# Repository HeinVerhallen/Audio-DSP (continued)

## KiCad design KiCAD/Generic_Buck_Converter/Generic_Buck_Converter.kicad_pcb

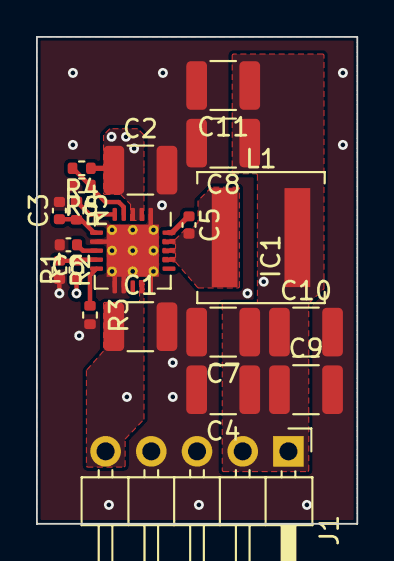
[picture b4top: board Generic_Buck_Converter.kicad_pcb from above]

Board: 4 copper layers, 17.8 x 27.0 mm, 20 parts (0 on the bottom side), 11 nets.

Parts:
C1, C2, C4, C7, C8, C9, C10, C11: C; C_1210_3225Metric
C3, C5, C6: C; C_0402_1005Metric
IC1: MAX17634C; TQFN-20-1EP_4x4mm_P0.5mm_EP2.9x2.9mm_ThermalVias_(JLCPCB_Co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
J1: Conn_01x05; PinHeader_1x05_P2.54mm_Horizontal
L1: L; L_Coilcraft_XAL6060-XXX
R1, R2, R3, R4, R5, R6: R; R_0402_1005Metric

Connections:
/Vin: C1.1, C2.1, IC1.2 (IN), IC1.3 (IN), IC1.14 (IN), J1.5, R4.1
/Vout: C4.1, C7.1, C8.1, C9.1, C10.1, C11.1, J1.1, J1.2, L1.2, R1.1
GND: C1.2, C2.2, C3.2, C4.2, C6.2, C7.2, C8.2, C9.2, C10.2, C11.2, IC1.1 (PGND), IC1.7 (SGND), IC1.11 (MODE/SYNC), IC1.12 (EXTVCC), IC1.15 (PGND), IC1.21 (EP), J1.3, J1.4, R2.2, R3.2, R6.2
unnamed: C5.2, IC1.17 (LX), IC1.18 (LX), IC1.19 (LX), L1.1
unnamed: C5.1, IC1.20 (BST)
unnamed: IC1.4 (EN/UVLO), R4.2, R6.1
unnamed: IC1.9 (FB), R1.2, R2.1
unnamed: C3.1, IC1.6 (INTVCC), R5.2
unnamed: IC1.5 (RESET), R5.1
unnamed: IC1.10 (RT), R3.1
unnamed: C6.1, IC1.8 (SS)

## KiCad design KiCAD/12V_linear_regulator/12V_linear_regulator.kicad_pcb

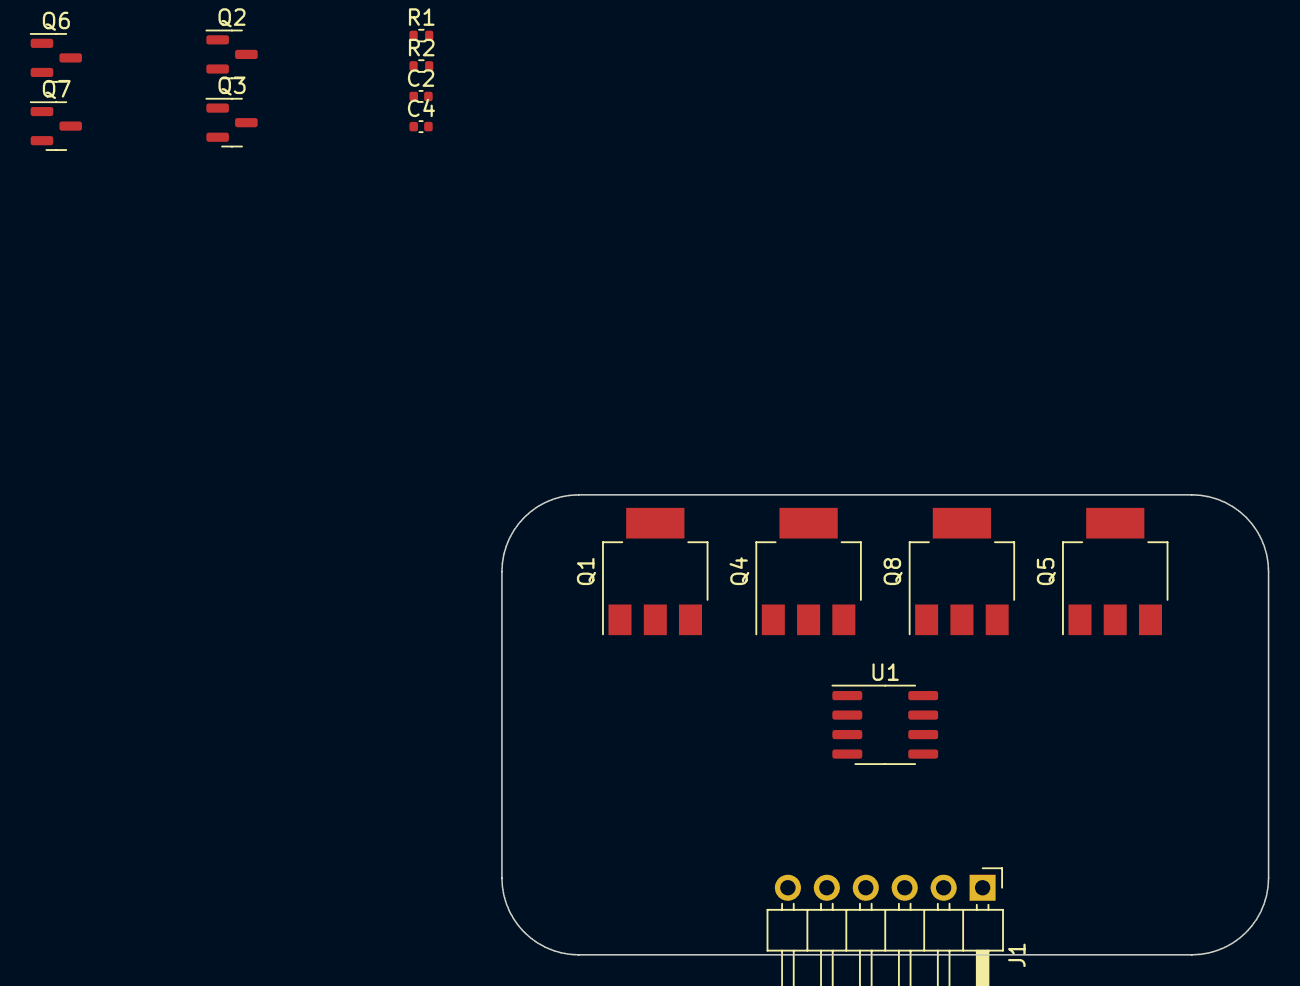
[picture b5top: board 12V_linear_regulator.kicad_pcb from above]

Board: 2 copper layers, 50.0 x 30.0 mm, 14 parts (0 on the bottom side), 8 nets, no tracks yet.

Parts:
C2, C4: 100p; C_0402_1005Metric
J1: Conn_01x06; PinHeader_1x06_P2.54mm_Horizontal
Q1, Q4: PZT2222AT3G; SOT-223
Q2, Q3: BC857; SOT-23
Q5, Q8: PZT2907AT3G; SOT-223
Q6, Q7: BC847; SOT-23
R1: 780R; R_0402_1005Metric
R2: 10k; R_0402_1005Metric
U1: LM4562; SOIC-8_3.9x4.9mm_P1.27mm

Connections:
+12V: J1.3, Q4.3
+15V: J1.1, Q1.2, Q1.4
GND: C4.2, J1.2, J1.5, R2.1
unnamed: C4.1, Q3.3 (C), U1.3 (+)
unnamed: Q2.1 (B), Q3.2 (E), R1.2
unnamed: Q2.3 (C), Q3.1 (B), R2.2
unnamed: Q1.3, Q2.2 (E), Q4.2, Q4.4, R1.1
unnamed: Q4.1, U1.1

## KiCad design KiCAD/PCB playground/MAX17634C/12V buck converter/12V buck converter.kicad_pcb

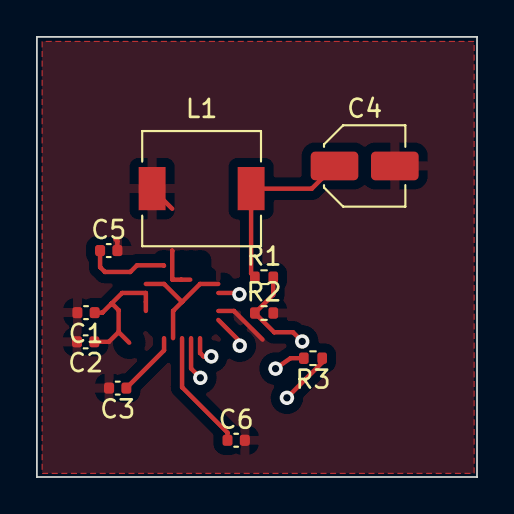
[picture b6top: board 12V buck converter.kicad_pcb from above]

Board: 4 copper layers, 24.5 x 24.5 mm, 10 parts (0 on the bottom side), 4 nets.

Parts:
C1, C2, C3, C5, C6: C; C_0402_1005Metric
C4: C; C_Elec_4x5.8
L1: L; L_6.3x6.3_H3
R1, R2, R3: R; R_0402_1005Metric

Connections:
/FB: R1.2, R2.1
/Vout: C4.1, L1.2, R1.1
Earth: C1.2, C2.2, C3.2, C4.2, C5.2, C6.2, L1.1, R2.2
unnamed: C1.1, C2.1

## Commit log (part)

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2023-04-13 Created audio sampler project
    Started with I2C protocol. Used I2C master from open-source file. Made initializer block which programs the WM8731 in the FPGA board using the I2C master block.
2023-04-13 Cleaned up
2023-04-15 Updated file structure to make it more clear
2023-04-17 Made the pdf of the SRD
2023-04-17 Updated SEPIC
2023-04-17 Added PCM1804
2023-04-18 Added symbol and footprint for general buck converter
2023-04-18 Worked on main board
2023-04-18 Add Generic PCB to Git
2023-04-18 Worked on KiCAD
2023-04-18 Worked a bit on the main board
2023-04-19 Update library, updated 3D model path
2023-04-19 fixed 3D viewer
2023-04-19 Push so we all have the same
2023-04-19 Updated main step
2023-04-19 2 codes for the i2s encoder
2023-04-19 Deleted the playground test
2023-04-20 fixed symbols excluding from board
2023-04-20 update kicad
2023-04-20 Buck PCB
2023-04-24 Update Audio sampler VHDL
    Created I2S encoder and decoder. Tested the code but the audio has a lot of noise.
2023-04-24 Updated Audio sampler VHDL
    Imported I2S_transceiver VHDL block from internet. This block uses the audio-codec inside the FPGA board as a slave. This has been tested and the audio is sampled correctly without any noise.
2023-04-24 Update Audio sampler
    Improved I2S encoder and decoder such that it now works. Tested with FPGA board and Audio came out correctly.
2023-04-25 Added 3D model 744871004
2023-04-25 Update Audio sampler
    Fixed bug where sampler worked at 32 bit but not at 24 bit. Now its able to sample at all bit resolutions. Saved .sof files for different scenarios.
2023-04-25 Made symbol and footprint for the FPGA board
2023-04-25 Update Audio sampler
    Created signal processor manager block.
    Created signal processor VHDL.
    Created shift register VHDL block.
    Implemented signal processor block with shift registers in signal processor manager.
2023-04-26 Worked on the linear voltage regulators
2023-04-28 Update SDD
    Wrote paragraph in architecture design chapter.
    Improved some text in system context design chapter.
2023-05-05 changes and additions to the sdd
    fixed a faulty piece of code in architecture and added stuff to UI
2023-05-08 kicad sepic update
2023-05-09 removed float specifier warning
2023-05-09 added parskip package
2023-05-09 Update SDD
    Update System architecture chapter
2023-05-09 Schematic orderlist update
2023-05-09 Updated background
2023-05-09 Worked on main board SCH
2023-05-10 Update SDD
    Updated architecture chapter
2023-05-10 Created Signal processor framework with FFT
2023-05-10 Created Matlab files for understanding FFT
2023-05-10 Worked on main board schematic
2023-05-10 Removed PDF files in Documentation folder
    Added pdf ignore in Documentation folder in Gitignore.
    Removed all PDF files in Documentation folder.
2023-05-10 Added black box representation
2023-05-11 Added Gerber + Excel-sheet
2023-05-16 Gerber_update
2023-05-16 Worked on SDD
2023-05-17 bestandsnaam wijziginen
2023-05-17 more pictuuuuures
2023-05-17 linear regulators changes
2023-05-22 update linear regulator pcb
2023-05-23 Matlab DFT with cosine and sine
    Created matlab script and simulink model to compute real and imaginary values of certain coefficients in input signal by multiplying input samples with sine and cosine for one period.
2023-05-23 Worked on main board schematic and PCB, added symbols to symbol library
2023-05-23 Worked on main board design
2023-05-24 linear
2023-05-24 Linear regulator schematic update
2023-05-24 update linear pcb
2023-05-24 Update fp-info-cache
2023-05-25 Matlab FFT + taylor series
    FFT_Radix2_DecimationInTime - Created first matlab tests where I implemented the FFT mathematics manually.
    TaylorSeries_sin_cos_generation - Updated the sinewave generation equation so it now works according to the horner mathematics.
2023-05-26 Test FPGA overclocking
    created new Quartus project to test PLL block capabilities to overclock the FPGA. This is possible up to a certain frequency. Highest frequency so far was 670MHz. See .sof files.
2023-05-30 Main board
2023-05-30 update linear and gerbers
2023-05-30 Mainboard buck_converter symbol update
2023-05-30 VU-meter design LTspice
2023-05-30 main PCB update DAC CH_1_2
2023-05-31 new gerbers
2023-05-31 added drill map files :)
2023-05-31 Completed ordering folder JLCPCB
2023-06-01 Test FPGA memory allocation VHDL
    Made a test program in VHDL to check how much memory is used by the FPGA for certain data arrays.
2023-06-05 Main board, ordering of PCBs and LTspice simulations
2023-06-05 Main PCB update
2023-06-05 Started UART protocol in VHDL
    Created a new quartus project for the UART protocol with the schematic of the basic blocks.
2023-06-05 created and tested uart parts
    the receiving and transmitting block have been coded and tested
    The TX buffer is no finished
    The RX buffer is not started
    the clock divider is not started
2023-06-06 Ad good as finilized the main board schematic
2023-06-06 Finalizer main board schematic exept passive order links. Schematic ready for review
2023-06-07 Updated UART protocol
    finished simulating the system
    the hardware test is yet to be performed
2023-06-07 Creation of final report (MDD)
    Created the Module Design Document
2023-06-08 Main brd
2023-06-08 Added STEP file
2023-06-08 main pcb
2023-06-08 Schematic send to Ralph for review
2023-06-12 Main board update
2023-06-13 PCB Main update
2023-06-13 Matlab Effects
    added the matlab effects me and youri made
2023-06-13 Created multiplication VHDL code
    Multiplication VHDL code is capable of doing unsigned multiplication and std_logic_vector multiplication.
2023-06-14 updated and simulink
2023-06-14 Updated order forms and ordered components 14-06-2023
2023-06-15 added stuff to the latex file
2023-06-16 Update multiplier_rounder.vhd
    Implemented unsigned, signed and STD_LOGIC_VECTOR multiplication functions. The unsigned and STD_LOGIC_VECTOR got to work in a very small time. But the signed one was very tricky. But in this version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
2023-06-16 Main board update ADC and DAC
2023-06-19 Worked on MDD
2023-06-19 Create BPF_filter.vhd
    Made BPF filter with state space.
    So far the computation of the discrete state space coefficients work.
    The compression of the larger binary value to a smaller one works now for unsigned values
2023-06-19 Update VHDL value compressor
    Finished the unsigned and signed value compress functions. They have been tested thoroughly with the according .do file.
    The functions are cleaned up and comments are added.
2023-06-20 a lot
2023-06-20 updated UIController
    added page navigation through buttons
2023-06-20 updated UI design
    added the new designs for the signal routing and presets
2023-06-21 added debounce resistor
2023-06-22 Divided Realization chapter into seperate files
2023-06-22 Updated name
2023-06-22 drastically increased MDD compile times
    decreased image resolution
2023-06-22 Created redesign of Audio DSP system block diagram
    Created redesign of Audio DSP system architecture block diagram with the new architecture design of the signal processor block
2023-06-22 Update Architecture chapter
    Added signal processor paragraph and effect explanation paragraph.
2023-06-23 Update MDD
    Added system context chapter from SDD and pasted that into sytem context.tex.
    Added argumentation for choosing distance between BPF bands for equalizer filter in Architecture chapter.
2023-06-24 added stuff, changed some stuff
2023-06-24 JO LEES OMSCHRIJVING
    heeft iemand enig idee waarom onze ToC niet zichtbaar is? Heb de titlepage info nu uit de .tex gehaalld en gewoon in de mainfile gezet. Maar dat doet hij ook nog steeds niet :/
2023-06-26 Update BPF filter VHDL
    Now able to compute state-space coefficients in VHDL correctly.
    Computation of state-space output does not work yet.
    Made test bench with sinewave generator as input.
2023-06-26 Stoemp alles in de git
    Want git doet weer moeilijk
2023-06-26 added schematics as appendices
    added schematic appendices
2023-06-26 fixed image in architecture, added stuff to concept development
2023-06-26 added ui pictures to the MDD image folder
2023-06-26 Update MDD
2023-06-26 updated UI design
2023-06-26 Added appendix file for schematics
2023-06-26 mijn appendix
2023-06-26 Update MDD
    Appendix update.
    Update firmware chapter
2023-06-26 Hoerezooi
2023-06-26 fixed references
2023-06-26 added all references
2023-06-26 finished UI chapter
2023-06-26 cleaned up the appendices
2023-06-26 research conclusions
2023-06-26 Conclusion and recommendation
2023-06-27 Updated main board. Ready to order now
2023-06-27 Ready to order PCB
2023-06-27 Update BPF VHDL
    Fixed bug where coefficient Bd is computed wrongly.
    Now the state-space filter works correct.
    Also the gain parameter can be configured correctly now.
2023-06-27 Updated results from BPF simulation
2023-06-28 nogmeer onzin
2023-07-03 Order forms and simulation model correction
2023-07-03 Added pictures
2023-07-04 updated UI
2023-07-04 sdram
2023-07-04 Update BPF + sinewave VHDL
    Implemented output available triggering correctly 180 degrees out of phase to the MCLK.
2023-07-05 Update Audio-sampler VHDL
    Implemented improved availability bit in I2S encoder and made it synthesizable. See resulting working simulation of Audio-dsp in this commit .pdf.
    BPF VHDL: moved signal state into process and made it a variable.
2023-07-05 update sdram
2023-07-05 Create BPF_filter_v3.vhd
    Created new version for fixed point implementation.
2023-07-05 sdram update
2023-07-06 Update Audio-DSP
    Updated BPF VHDL a bit.
    Created effect controller and volume effect.
    Generated multiple .sof files of the Audio-DSP system. Including a .jic file of a highgain version that works.
2023-07-10 Update BPF VHDL
    Updated BPF such that the nrst is implemented. Still does not work. We have chosen not to continue debugging the BPF.
    Fixed bug in the Initializer block where the index is not reset when the block is reset. Now the system can be reset correctly and restarts correctly.
2023-07-10 Update Audio-DSP
    Fixed bug in clock divider VHDL. Now the clock has 50% duty cycle.
    Remade I2S encoder and decoder in V2. They now dont use the handshake protocol anymore.
    Remade volume effect such that it now works continuous. Fixed bug in gain lookup table. It is now a constant and the values are now limited to three decimals.
    The volume effect can also be controlled with switched and this has worked, see .sof files.
2023-07-10 Update BPF VHDL
    Made a new schematic file in quartus to test the system with the BPF. Tried to fix it by making the gain lookup table a constant but it still just gives out noise a lot. The music can be heard very l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
    So skip the BPF and focus on the report.
2023-07-10 FPGA GPIO measurements
2023-07-11 Update MDD
    Revisited bit assignments for effect parameters in Architecture chapter.
    Added signal processing book and active bpf tutorial to references.
2023-07-11 Pictures
2023-07-11 updated files
2023-07-11 probably fully functional encoder
2023-07-11 update delay effect
2023-07-12 semi working decoder
2023-07-12 Update Volume control VHDL
    Made test bench for volume controller. Tests were successful.
2023-07-12 Added verficiation appendix
2023-07-12 menu fix
    still some bug in touchscreen
2023-07-12 Update MDD realization_firmware
    Added text over volume control effect and distortion effect. Added image to show saturation effect.
    Fixed some text over flanger, chorus and delay effects.
2023-07-12 updated UI + added UI code
2023-07-12 Updated report contribution table
2023-07-12 Update main.tex
    Made bibliography with capital first letter
2023-07-12 updated titlepage and research
2023-07-12 Update MDD
    Updated titlepage.
    Added simulation results. Moved simulation results to new appendix file.
2023-07-12 Update Verification.tex
    Removed SEPIC subsubsection.
    Fixed some references and typos.
2023-07-12 Updated main
2023-07-12 Update Verification.tex
    Added more text to the different firmware parts.
    Written firmware conclusion in verification.
2023-07-12 Update ref.bib
    Removed dumb ECG project report from references.
2023-07-12 Update UserInterface.tex
    Replaced hard coded reference with correct one
